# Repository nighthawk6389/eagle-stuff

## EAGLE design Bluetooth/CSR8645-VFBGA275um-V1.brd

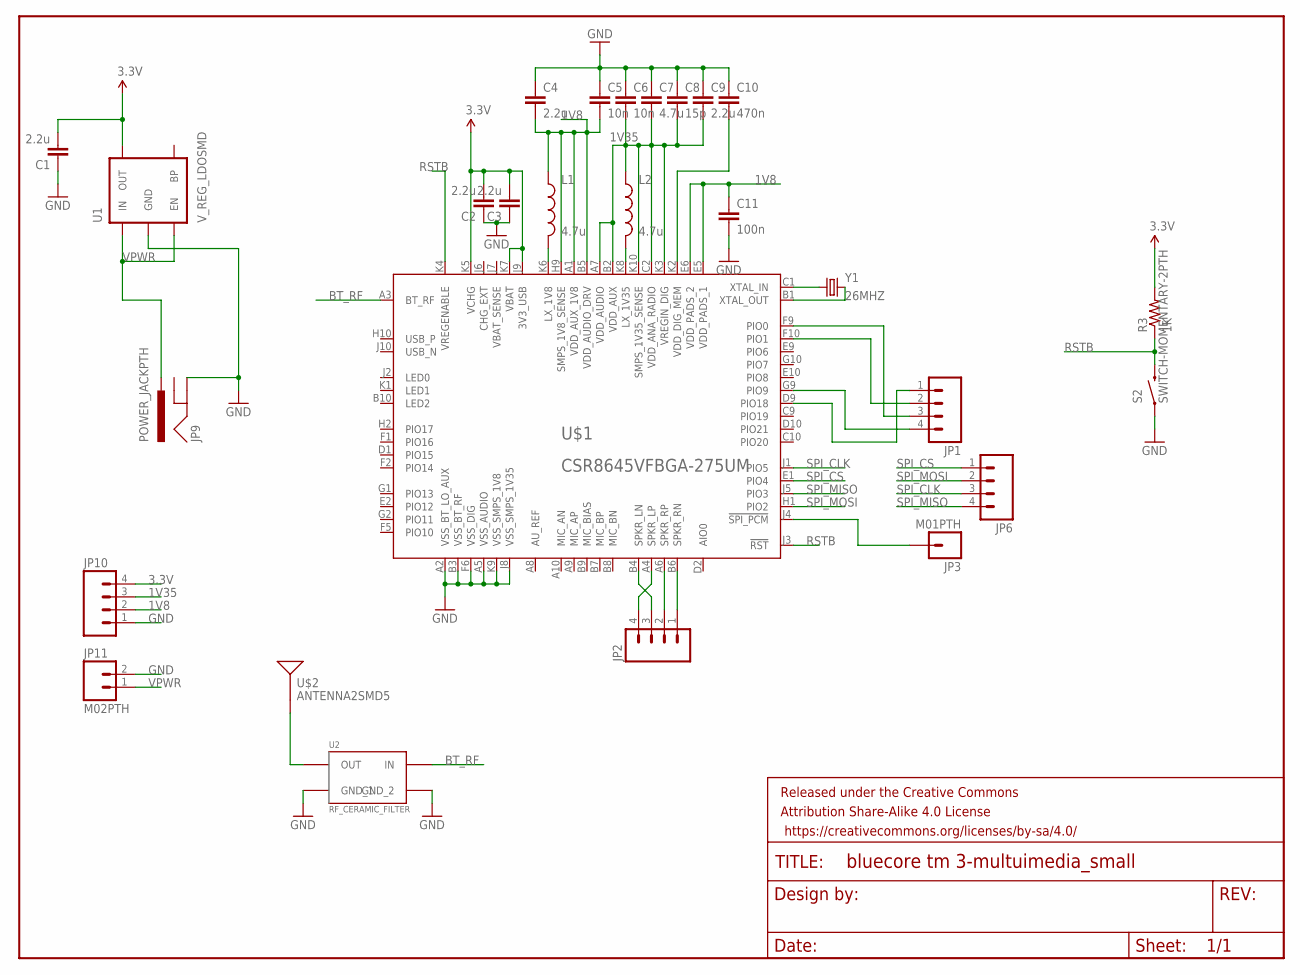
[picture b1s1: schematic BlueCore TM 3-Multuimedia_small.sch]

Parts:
C1, C2, C3, C4, C9: 2.2u; CAP-PTH-SMALL
C5, C6: 10n; CAP-PTH-SMALL
C7: 4.7u; CAP-PTH-SMALL
C8: 15p; CAP-PTH-SMALL
C10: 470n; CAP-PTH-SMALL
C11: 100n; CAP-PTH-SMALL
FRAME1: FRAME-LETTER; CREATIVE_COMMONS
JP1, JP2, JP6, JP10: M04PTH; 1X04
JP3: M01PTH; 1X01
JP9: POWER_JACKPTH; POWER_JACK_PTH
JP11: M02PTH; 1X02
L1, L2: 4.7u; 0805
R3: 1K; 0805
S2: SWITCH-MOMENTARY-2PTH; TACTILE-PTH
U1: V_REG_LDOSMD; SOT23-5
U2: RF_CERAMIC_FILTER; RF_FILTER
U$1: CSR8645VFBGA-275UM; VFBGA68-LARGE
U$2: ANTENNA2SMD5; ANTENNA-CHIP5
Y1: 26MHZ; HC49US

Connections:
1V8: C4.2, C5.2, C11.1, JP10.2, L1.1, U$1.A1 (VDD_AUX_1V8), U$1.B5 (VDD_AUDIO_DRV), U$1.E5 (VDD_PADS_1), U$1.E6 (VDD_PADS_2), U$1.H9 (SMPS_1V8_SENSE)
1V35: C6.2, C7.2, C8.2, C9.2, JP10.3, L2.1, U$1.A7 (VDD_AUDIO), U$1.B2 (VDD_AUX), U$1.C2 (VDD_ANA_RADIO), U$1.K3 (VREGIN_DIG), U$1.K10 (SMPS_1V35_SENSE)
3.3V: C1.2, C2.2, C3.2, JP10.4, R3.2, U1.5 (OUT), U$1.J9 (3V3_USB), U$1.K5 (VCHG), U$1.K7 (VBAT)
!SPI_PCM: JP3.1, U$1.J4 (!SPI_PCM)
BT_RF: U2.4 (IN), U$1.A3 (BT_RF)
GND: C1.1, C2.1, C3.1, C4.1, C5.1, C6.1, C7.1, C8.1, C9.1, C10.1, C11.2, JP9.GND, JP10.1, JP11.2, S2.1, U1.2 (GND), U2.1 (GND_1), U2.3 (GND_2), U$1.A2 (VSS_BT_LO_AUX), U$1.A5 (VSS_AUDIO), U$1.B3 (VSS_BT_RF), U$1.F6 (VSS_DIG), U$1.J8 (VSS_SMPS_1V35), U$1.K9 (VSS_SMPS_1V8)
unnamed: JP1.3, U$1.F9 (PIO0)
unnamed: JP2.3, U$1.B4 (SPKR_LN)
unnamed: L1.2, U$1.K6 (LX_1V8)
unnamed: L2.2, U$1.K8 (LX_1V35)
unnamed: U$1.C1 (XTAL_IN), Y1.1
unnamed: C10.2, U$1.K2 (VDD_DIG_MEM)
unnamed: U$1.B1 (XTAL_OUT), Y1.2
unnamed: JP1.2, U$1.F10 (PIO1)
unnamed: JP1.1, U$1.D9 (PIO18)
unnamed: JP2.4, U$1.A4 (SPKR_LP)
unnamed: JP1.4, U$1.G9 (PIO9)
unnamed: JP2.2, U$1.A6 (SPKR_RP)
unnamed: U2.2 (OUT), U$2.FEED
unnamed: JP2.1, U$1.B6 (SPKR_RN)
RSTB: R3.1, S2.3 (2), U$1.J3 (!RST), U$1.K4 (VREGENABLE)
SPI_CLK: JP6.3, U$1.J1 (PIO5)
SPI_CS: JP6.1, U$1.E1 (PIO4)
SPI_MISO: JP6.4, U$1.J5 (PIO3)
SPI_MOSI: JP6.2, U$1.H1 (PIO2)
VPWR: JP9.PWR, JP11.1, U1.1 (IN), U1.3 (EN)

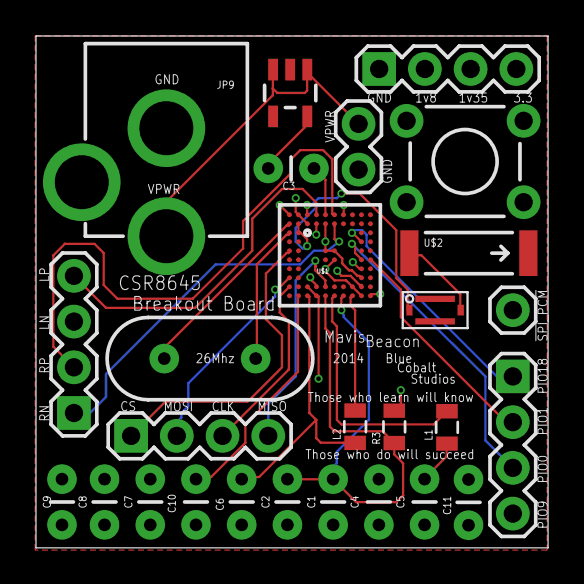
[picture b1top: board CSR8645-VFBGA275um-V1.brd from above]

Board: 4 copper layers, 28.4 x 28.4 mm, 28 parts (0 on the bottom side), 26 nets.

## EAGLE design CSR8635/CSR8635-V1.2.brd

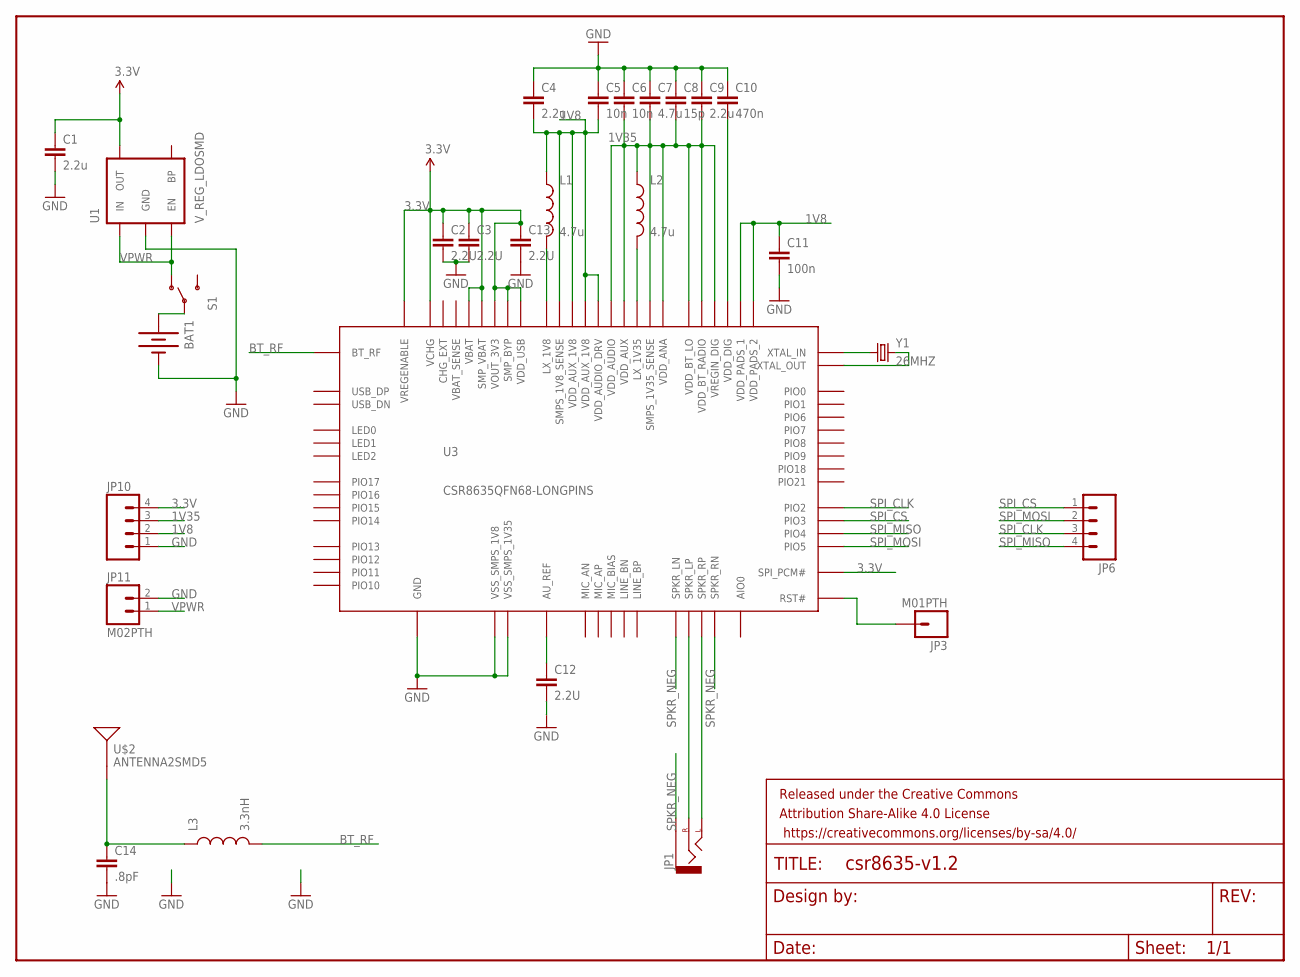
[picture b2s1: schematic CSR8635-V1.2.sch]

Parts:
BAT1: BATTERY9V; BATTCON_9V
C1, C4, C9: 2.2u; 0603-CAP
C2, C3, C12, C13: 2.2U; 0603-CAP
C5, C6: 10n; 0603-CAP
C7: 4.7u; 0603-CAP
C8: 15p; 0603-CAP
C10: 470n; 0603-CAP
C11: 100n; 0603-CAP
C14: .8pF; 0603-CAP
FRAME1: FRAME-LETTER; CREATIVE_COMMONS
JP1: AUDIO-JACKSMD2; AUDIO-JACK-3.5MM-SMD
JP3: M01PTH; 1X01
JP6, JP10: M04PTH; 1X04
JP11: M02PTH; 1X02
L1, L2: 4.7u; 0805
L3: 3.3nH; 0805
S1: SWITCH-SPDTPTH; SWITCH-SPDT
U1: V_REG_LDOSMD; SOT23-5
U3: CSR8635QFN68-LONGPINS; QFN68
U$2: ANTENNA2SMD5; ANTENNA-CHIP5
Y1: 26MHZ; HC49US

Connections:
1V8: C4.2, C5.2, C11.1, JP10.2, L1.1, U3.8 (VDD_AUDIO_DRV), U3.15 (VDD_AUX_1V8), U3.16 (VDD_AUX_1V8), U3.33 (VDD_PADS_1), U3.53 (SMPS_1V8_SENSE), U3.63 (VDD_PADS_2)
1V35: C6.2, C7.2, C8.2, C9.2, JP10.3, L2.1, U3.3 (VDD_AUDIO), U3.11 (VDD_BT_RADIO), U3.13 (VDD_BT_LO), U3.14 (VDD_AUX), U3.17 (VDD_ANA), U3.39 (VREGIN_DIG), U3.52 (SMPS_1V35_SENSE)
3.3V: C1.1, C2.1, C3.1, C13.1, JP10.4, U1.5 (OUT), U3.29 (SPI_PCM#), U3.40 (VREGENABLE), U3.41 (VOUT_3V3), U3.42 (VCHG), U3.45 (VBAT), U3.48 (SMP_VBAT), U3.49 (SMP_BYP), U3.54 (VDD_USB)
!SPI_PCM: JP3.1, U3.35 (RST#)
BT_RF: L3.2, U3.12 (BT_RF)
GND: BAT1.-, C1.2, C2.2, C3.2, C4.1, C5.1, C6.1, C7.1, C8.1, C9.1, C10.1, C11.2, C12.2, C13.2, C14.2, JP10.1, JP11.2, U1.2 (GND), U3.46 (VSS_SMPS_1V8), U3.51 (VSS_SMPS_1V35), U3.CNTR (GND), U3.CNTR1 (GND), U3.CNTR2 (GND), U3.CNTR3 (GND)
unnamed: BAT1.+, S1.2
unnamed: JP1.RING (RIGHT), U3.10 (SPKR_LP)
unnamed: L1.2, U3.47 (LX_1V8)
unnamed: U3.19 (XTAL_IN), Y1.1
unnamed: L2.2, U3.50 (LX_1V35)
unnamed: C10.2, U3.38 (VDD_DIG)
unnamed: U3.18 (XTAL_OUT), Y1.2
unnamed: JP1.TIP (LEFT), U3.7 (SPKR_RP)
unnamed: C12.1, U3.1 (AU_REF)
unnamed: C14.1, L3.1, U$2.FEED
SPI_CLK: JP6.3, U3.30 (PIO2)
SPI_CS: JP6.1, U3.28 (PIO3)
SPI_MISO: JP6.4, U3.24 (PIO4)
SPI_MOSI: JP6.2, U3.34 (PIO5)
SPKR_NEG: JP1.SLEEVE, U3.6 (SPKR_RN), U3.9 (SPKR_LN)
VPWR: JP11.1, S1.1 (O), U1.1 (IN), U1.3 (EN)

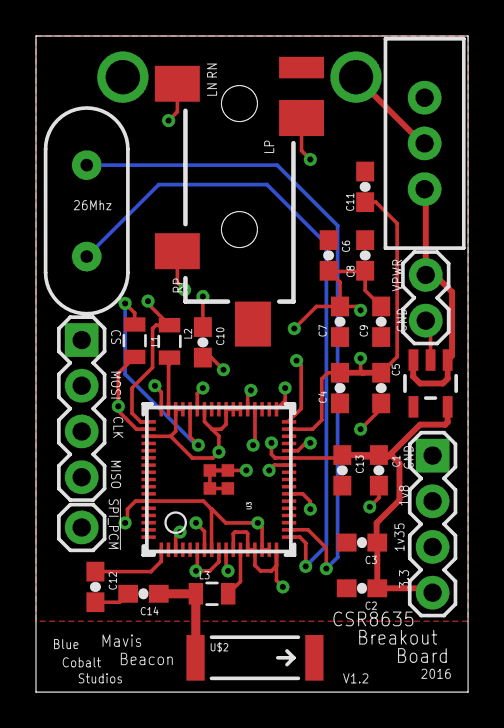
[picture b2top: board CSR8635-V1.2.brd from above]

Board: 4 copper layers, 24.0 x 36.4 mm, 29 parts (1 on the bottom side), 22 nets.

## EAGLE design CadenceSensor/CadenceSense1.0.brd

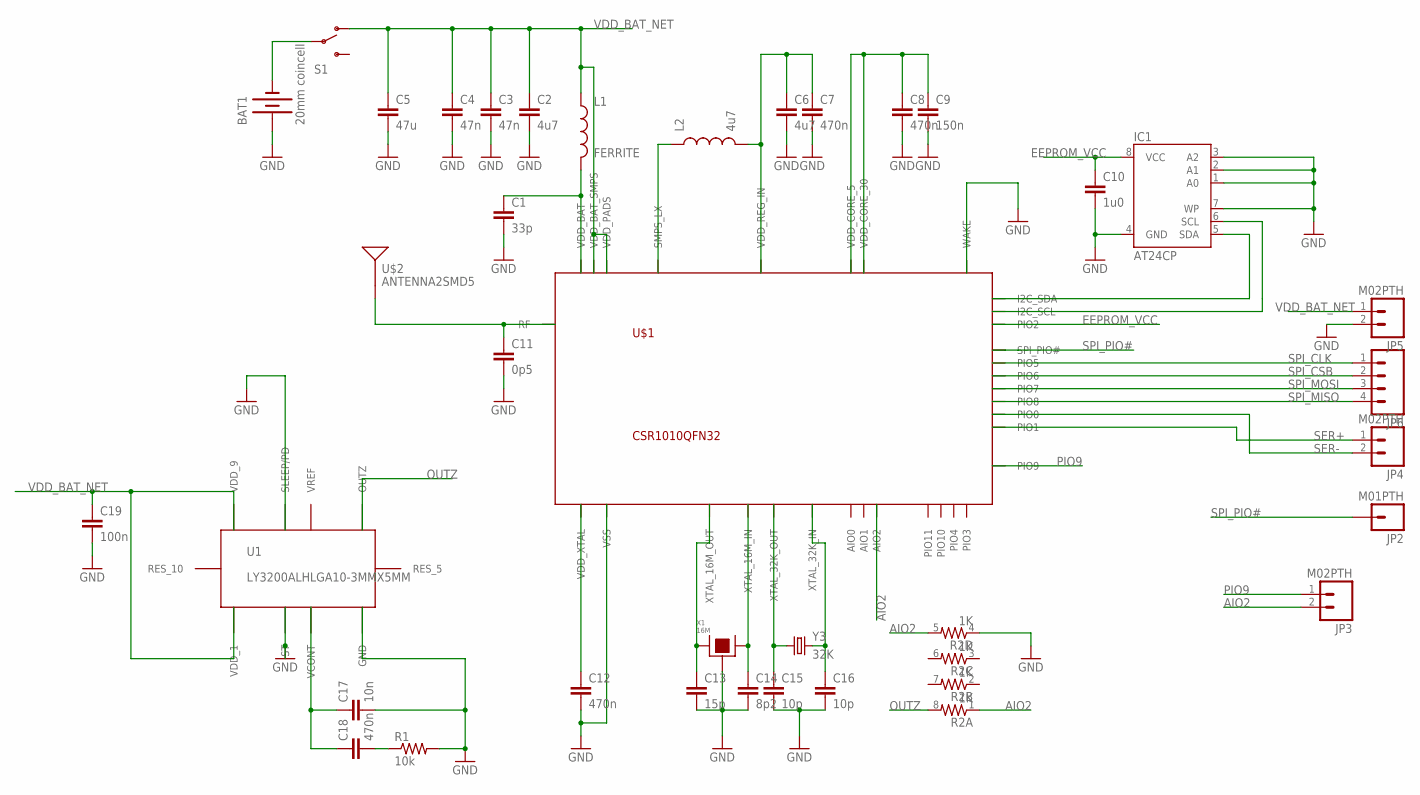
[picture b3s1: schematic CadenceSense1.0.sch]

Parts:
BAT1: 20mm coincell; BATTCON_20MM_4LEGS
C1: 33p; 0603-CAP
C2, C6: 4u7; 0603-CAP
C3, C4: 47n; 0603-CAP
C5: 47u; 0603-CAP
C7, C8, C12, C18: 470n; 0603-CAP
C9: 150n; 0603-CAP
C10: 1u0; 0603-CAP
C11: 0p5; 0603-CAP
C13: 15p; 0603-CAP
C14: 8p2; 0603-CAP
C15, C16: 10p; 0603-CAP
C17: 10n; 0603-CAP
C19: 100n; 0603-CAP
IC1: AT24CP; DIL08
JP2: M01PTH; 1X01
JP3, JP4, JP5: M02PTH; 1X02
JP6: M04PTH; 1X04
L1: FERRITE; 0805
L2: 4u7; 0805
R1: 10k; 0603-RES
R2: 1K; 0603-ARV
S1: SWITCH-SPDTPTH; SWITCH-SPDT
U1: LY3200ALHLGA10-3MMX5MM; LGA10
U$1: CSR1010QFN32; QFN-32
U$2: ANTENNA2SMD5; ANTENNA-CHIP5
X1: 16M; TSX-3225
Y3: 32K; CRYSTAL-32KHZ-SMD_EPSON_MC146

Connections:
AIO2: JP3.2, R2.1, R2.5 (2), U$1.11 (AIO2)
EEPROM_VCC: C10.1, IC1.8 (VCC), U$1.27 (PIO2)
GND: BAT1.1 (+), C1.2, C2.2, C3.2, C4.2, C5.2, C6.2, C7.2, C8.2, C9.2, C10.2, C11.2, C12.2, C13.2, C14.2, C15.2, C16.2, C17.2, C19.2, IC1.1 (A0), IC1.2 (A1), IC1.3 (A2), IC1.4 (GND), IC1.7 (WP), JP5.2, R1.2, R2.4 (1), U1.2 (ST), U1.4 (GND), U1.8 (SLEEP/PD), U$1.4 (WAKE), U$1.EP (VSS), X1.2, X1.4
unnamed: BAT1.2 (-), S1.2
unnamed: C6.1, C7.1, L2.2, U$1.6 (VDD_REG_IN)
unnamed: C1.1, L1.2, U$1.1 (VDD_BAT)
unnamed: C11.1, U$1.7 (RF), U$2.FEED
unnamed: C16.1, U$1.3 (XTAL_32K_IN), Y3.P$1 (2)
unnamed: L2.1, U$1.31 (SMPS_LX)
unnamed: C8.1, C9.1, U$1.5 (VDD_CORE_5), U$1.30 (VDD_CORE_30)
unnamed: C15.1, U$1.2 (XTAL_32K_OUT), Y3.P$2 (1)
unnamed: C14.1, U$1.10 (XTAL_16M_IN), X1.3
unnamed: IC1.5 (SDA), U$1.29 (I2C_SDA)
unnamed: IC1.6 (SCL), U$1.28 (I2C_SCL)
unnamed: C13.1, U$1.9 (XTAL_16M_OUT), X1.1
unnamed: C12.1, U$1.8 (VDD_XTAL)
unnamed: C17.1, C18.1, U1.3 (VCONT)
unnamed: C18.2, R1.1
OUTZ: R2.8 (2), U1.6 (OUTZ)
PIO9: JP3.1, U$1.23 (PIO9)
SER+: JP4.1, U$1.15 (PIO1)
SER-: JP4.2, U$1.14 (PIO0)
SPI_CLK: JP6.1, U$1.18 (PIO5)
SPI_CSB: JP6.2, U$1.19 (PIO6)
SPI_MISO: JP6.4, U$1.22 (PIO8)
SPI_MOSI: JP6.3, U$1.20 (PIO7)
SPI_PIO#: JP2.1, U$1.26 (SPI_PIO#)
VDD_BAT_NET: C2.1, C3.1, C4.1, C5.1, C19.1, JP5.1, L1.1, S1.1 (O), U1.1 (VDD_1), U1.9 (VDD_9), U$1.21 (VDD_PADS), U$1.32 (VDD_BAT_SMPS)

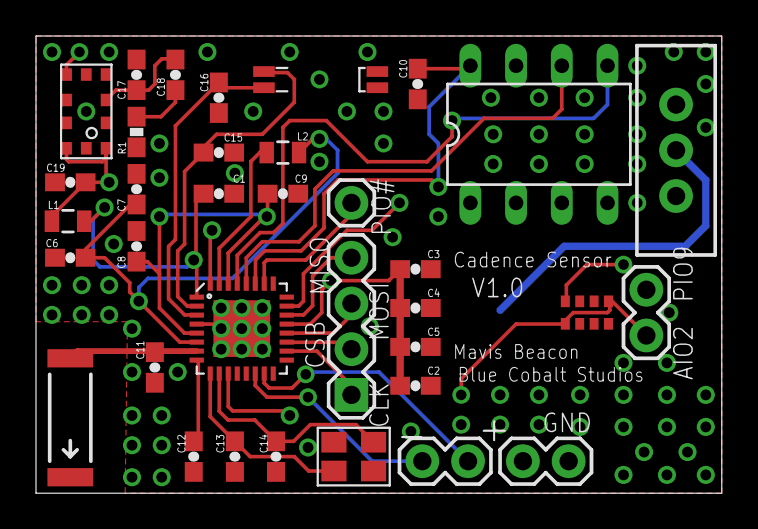
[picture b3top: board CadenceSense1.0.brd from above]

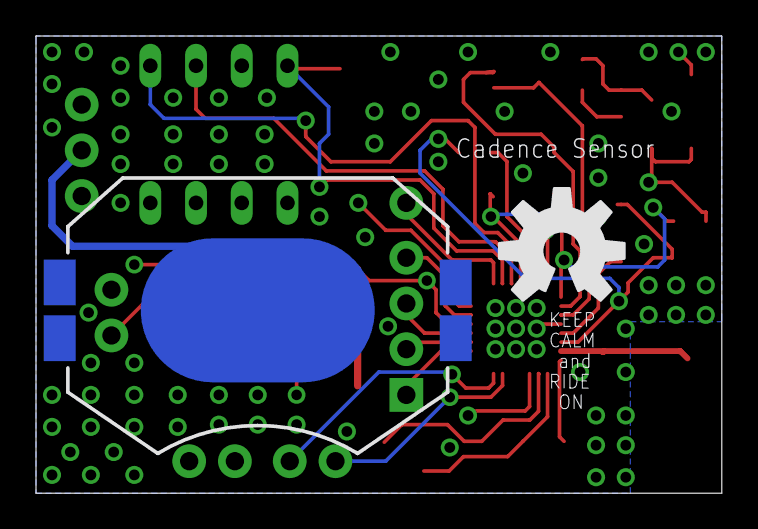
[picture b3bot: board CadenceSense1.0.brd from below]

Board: 4 copper layers, 38.1 x 25.4 mm, 37 parts (2 on the bottom side), 28 nets.

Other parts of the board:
U$3: OSHW-LOGO-L

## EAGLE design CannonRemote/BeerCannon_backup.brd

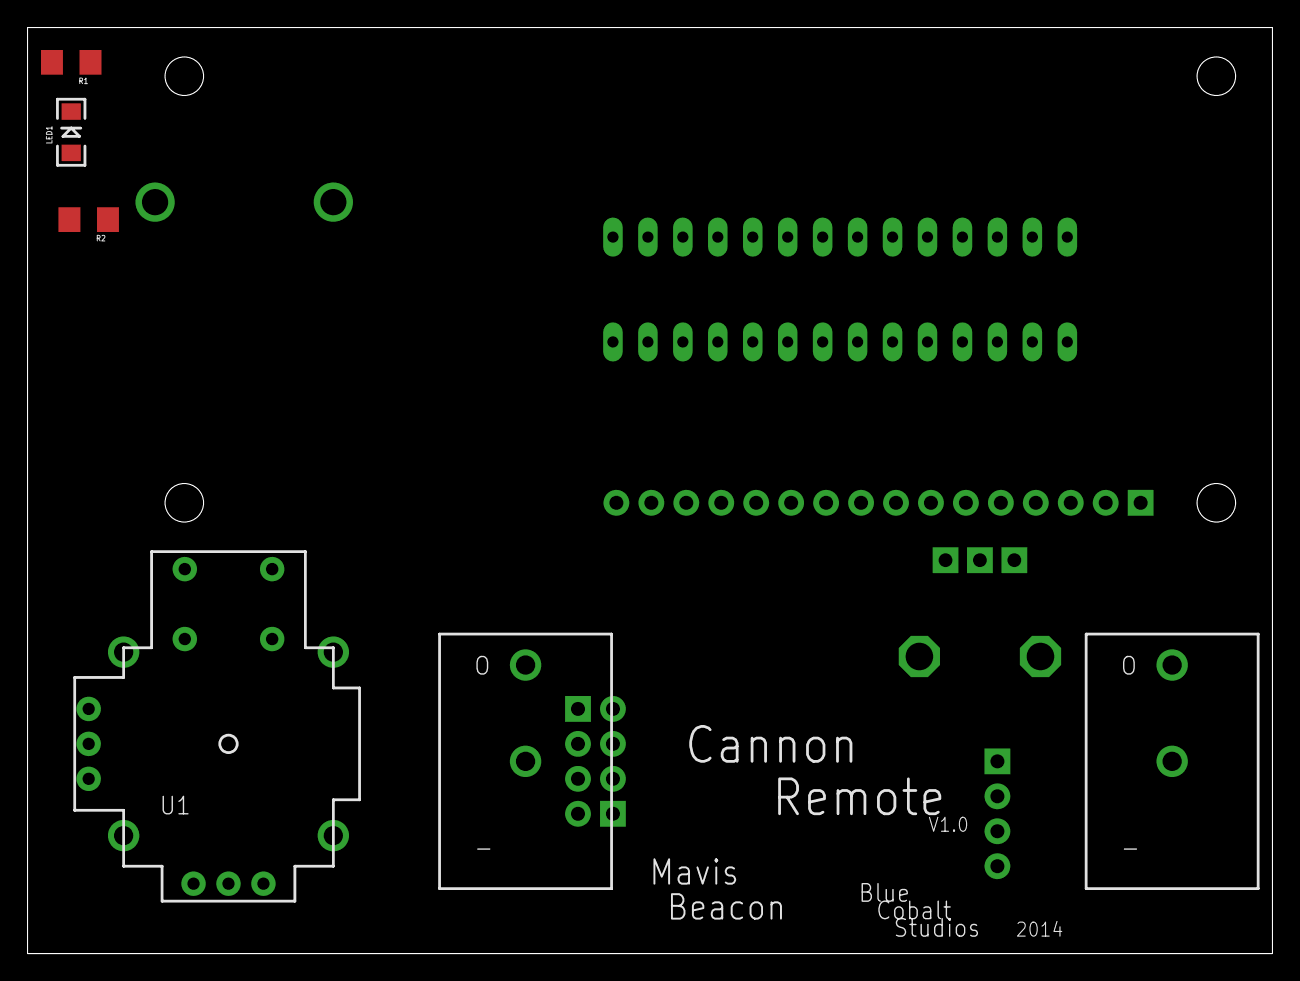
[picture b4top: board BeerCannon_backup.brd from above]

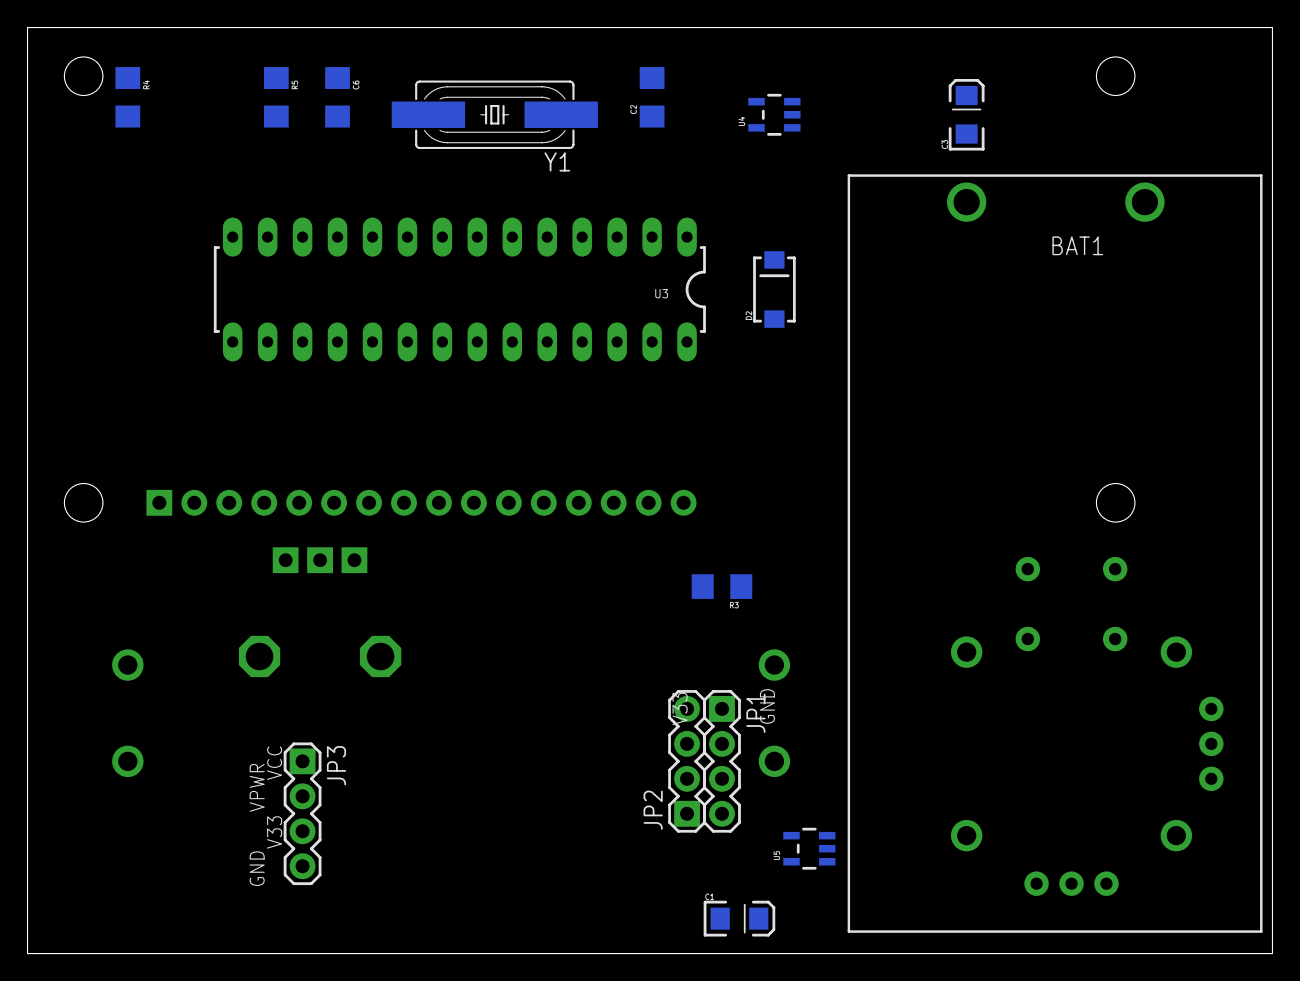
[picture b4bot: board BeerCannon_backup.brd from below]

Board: 2 copper layers, 90.5 x 67.3 mm, 25 parts (17 on the bottom side), 29 nets, no tracks yet.

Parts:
BAT1: BATTCON_9V
C1, C3: EIA3216
C2, C6: 1206
D2: SMA-DIODE
FRAME1: FRAME-LETTER; CREATIVE_COMMONS
JP1, JP2, JP3: 1X04
LED1: LED-1206
R1, R2, R3, R4, R5: 1206
RV1: ALPS_POT
U1: JOYSTICKPTH; JOYSTICK
U2: LCD-16X2NOSILK; LCD-16X2_NOSILK
U3: ATMEGA328P_PDIP; DIL28-3
U4, U5: V_REG_LDOSMD; SOT23-5
U$1, U$2: SWITCH-SPST-2TV; SWITCH-SPST-VERTICAL
Y1: HC49UP

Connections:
ANALOG1: R3.2, U3.24
ANALOG2: U1.H2, U3.25
ANALOG3: U1.V2, U3.26
CE: JP1.2, U3.15
CSN: JP2.3, U3.16
DIG6: U2.6, U3.12
DIG7: U2.4, U3.13
GND: BAT1.+, C1.A, C2.1, C3.A, C6.1, JP1.1, JP3.4, R1.2, R5.1, U1.H3, U1.V3, U2.2, U3.8, U3.22, U4.2, U5.2
MISO: JP1.4, U3.18
MOSI: JP2.2, U3.17
unnamed: LED1.C, R1.1
unnamed: D2.A, U$2.1
unnamed: R3.1, U1.B2A
unnamed: R2.1, U3.1
unnamed: R4.2, U$1.2
unnamed: C2.2, U3.9, Y1.1
unnamed: C6.2, U3.10, Y1.2
unnamed: D2.C, U4.1, U4.3
unnamed: RV1.P$2, U2.3
unnamed: R4.1, R5.2, U3.14
unnamed: RV1.P$1, U2.5
PIN4: U2.14, U3.4
PIN5: U2.13, U3.5
PIN6: U2.12, U3.6
PIN11: U2.11, U3.11
SCK: JP1.3, U3.19
V33: C1.C, JP2.4, JP3.3, U5.5
VCC: BAT1.-, JP3.1, U5.1, U5.3, U$2.2
VPWR: C3.C, JP3.2, LED1.A, R2.2, RV1.P$3, U1.B1A, U1.H1, U1.V1, U2.1, U3.7, U3.20, U4.5, U$1.1

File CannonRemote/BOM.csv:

Part,Value,Device,Package,Description,,
BAT1,,BATTERY9V,BATTCON_9V,Battery Holders,,
C1,,CAP_POL1206,EIA3216,Capacitor Polarized,2.2uf,
C2,,CAP1206,1206,Capacitor,22pf,
C3,,CAP_POL1206,EIA3216,Capacitor Polarized,2.2uf,299-3690-1-nd
C6,,CAP1206,1206,Capacitor,22pf,399-11987-1-nd
D2,,DIODESMA,SMA-DIODE,Diode,,s1afsct-nd
,,,,,,
JP1,,M04PTH,1X04,Header 4,,
JP2,,M04PTH,1X04,Header 4,,
JP3,,M04PTH,1X04,Header 4,,
LED1,,LED1206,LED-1206,LEDs,,
R1,,RESISTOR1206,1206,Resistor,180,
R2,,RESISTOR1206,1206,Resistor,1k,
R3,,RESISTOR1206,1206,Resistor,1k,need to be pulldown
R5,,RESISTOR1206,1206,Resistor,10k,
RV1,,POT,ALPS_POT,,,
U$1,SWITCH-SPST-2TV,SWITCH-SPST-2TV,SWITCH-SPST-VERTICAL,,,
U$2,SWITCH-SPST-2TV,SWITCH-SPST-2TV,SWITCH-SPST-VERTICAL,,,
U1,JOYSTICKPTH,JOYSTICKPTH,JOYSTICK,Thumb Joystick,,
U2,LCD-16X2NOSILK,LCD-16X2NOSILK,LCD-16X2_NOSILK,Standard text-only 16x2 parallel input LCD,,
U3,ATMEGA328P_PDIP,ATMEGA328P_PDIP,DIL28-3,uC used in the Arduino,,
U4,V_REG_LDOSMD,V_REG_LDOSMD,SOT23-5,Voltage Regulator LDO,5V,
U5,V_REG_LDOSMD,V_REG_LDOSMD,SOT23-5,Voltage Regulator LDO,3.3V,
Y1,,CRYSTALSMD,HC49UP,Various standard crystals. Proven footprints.,,

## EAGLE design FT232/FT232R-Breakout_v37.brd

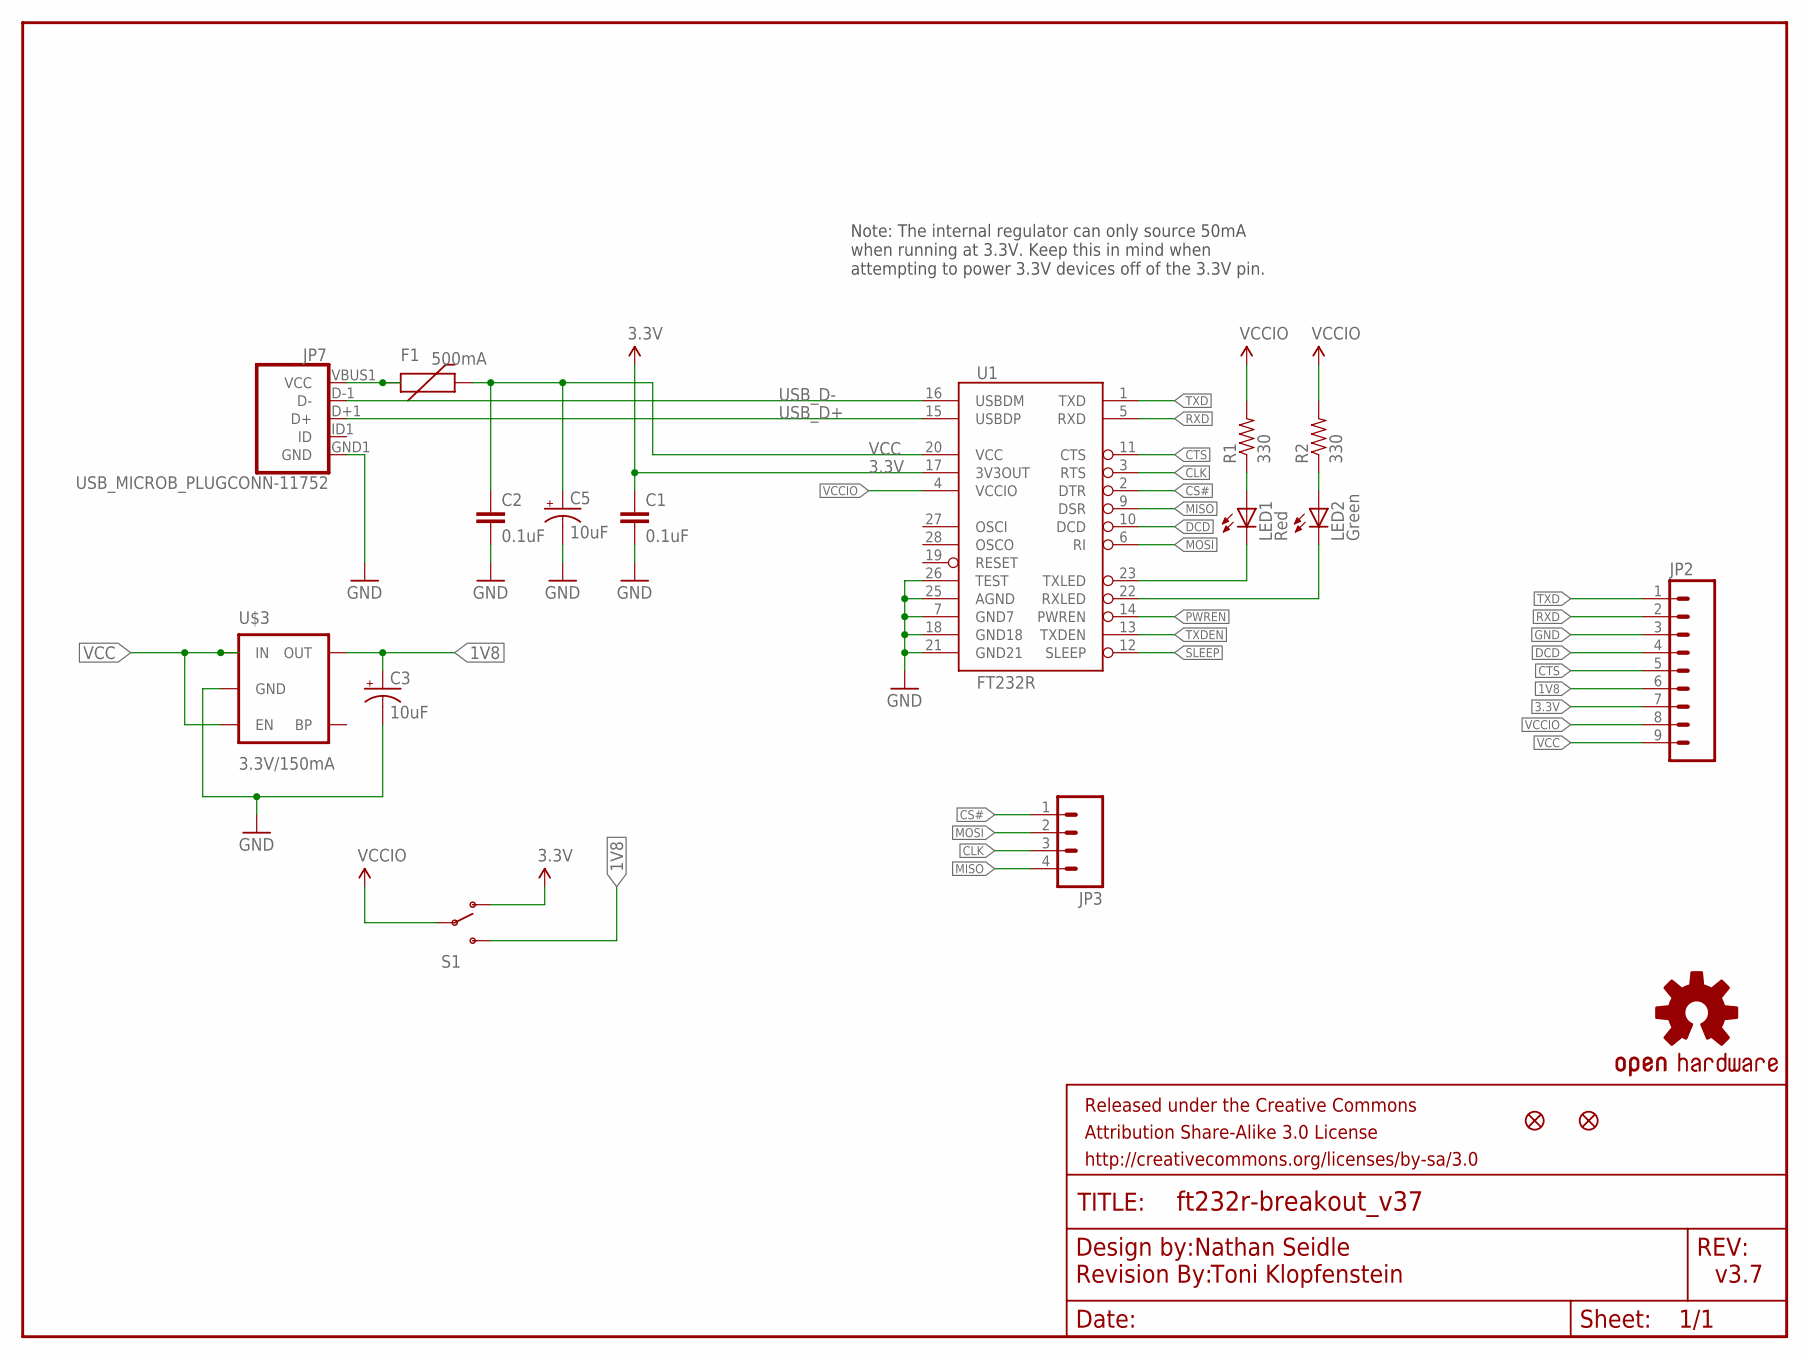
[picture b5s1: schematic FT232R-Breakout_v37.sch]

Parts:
C1, C2: 0.1uF; 0603-CAP
C3, C5: 10uF; EIA3216
F1: 500mA; PTC-1206
FRAME1: FRAME-LETTER; CREATIVE_COMMONS
JP2: M09; 1X09
JP3: M04PTH; 1X04
JP5, JP6: FIDUCIAL1X2; FIDUCIAL-1X2
JP7: USB_MICROB_PLUGCONN-11752; USB-B-MICRO-SMD_V03
LED1: Red; LED-0603
LED2: Green; LED-0603
LOGO1: OSHW-LOGOS; OSHW-LOGO-S
R1, R2: 330; 0603-RES
S1: SWITCH-SPDTSMD; AYZ0202
U1: FT232R; SSOP28DB
U$1: REVISION
U$3: 3.3V/150mA; SOT23-5

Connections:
1V8: C3.A (+), JP2.6, S1.3 (S), U$3.5 (OUT)
3.3V: C1.1, JP2.7, S1.1 (O), U1.17 (3V3OUT)
CLK: JP3.3, U1.3 (RTS)
CS#: JP3.1, U1.2 (DTR)
CTS: JP2.5, U1.11 (CTS)
DCD: JP2.4, U1.10 (DCD)
GND: C1.2, C2.2, C3.C (-), C5.C (-), JP2.3, JP7.GND1 (GND), U1.7 (GND7), U1.18 (GND18), U1.21 (GND21), U1.25 (AGND), U1.26 (TEST), U$3.2 (GND)
MISO: JP3.4, U1.9 (DSR)
MOSI: JP3.2, U1.6 (RI)
unnamed: LED1.A, R1.1
unnamed: LED2.A, R2.1
unnamed: F1.1, JP7.VBUS1 (VCC)
PWREN: U1.14 (PWREN)
RXD: JP2.2, U1.5 (RXD)
RXLED: LED2.C, U1.22 (RXLED)
SLEEP: U1.12 (SLEEP)
TXD: JP2.1, U1.1 (TXD)
TXDEN: U1.13 (TXDEN)
TXLED: LED1.C, U1.23 (TXLED)
USB_D+: JP7.D+1 (D+), U1.15 (USBDP)
USB_D-: JP7.D-1 (D-), U1.16 (USBDM)
VCC: C2.1, C5.A (+), F1.2, JP2.9, U1.20 (VCC), U$3.1 (IN), U$3.3 (EN)
VCCIO: JP2.8, R1.2, R2.2, S1.2, U1.4 (VCCIO)

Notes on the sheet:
v3.7
Nathan Seidle
Toni Klopfenstein
Note: The internal regulator can only source 50mA when running at 3.3V. Keep this in mind when attempting to power 3.3V devices off of the 3.3V pin.

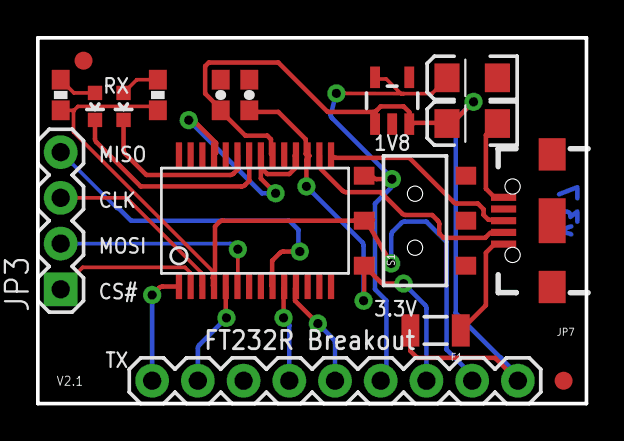
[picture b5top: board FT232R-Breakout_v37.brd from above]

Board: 2 copper layers, 30.5 x 20.3 mm, 20 parts (1 on the bottom side), 20 nets.

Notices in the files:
parts and their libraries:
SparkFun-Aesthetics: Licensing: Creative Commons ShareAlike 4.0 International - https://creativecommons.org/licenses/by-sa/4.0
SparkFun-Aesthetics: Released under the Creative Commons Attribution Share-Alike 4.0 License
SparkFun-Aesthetics: https://creativecommons.org/licenses/by-sa/4.0
